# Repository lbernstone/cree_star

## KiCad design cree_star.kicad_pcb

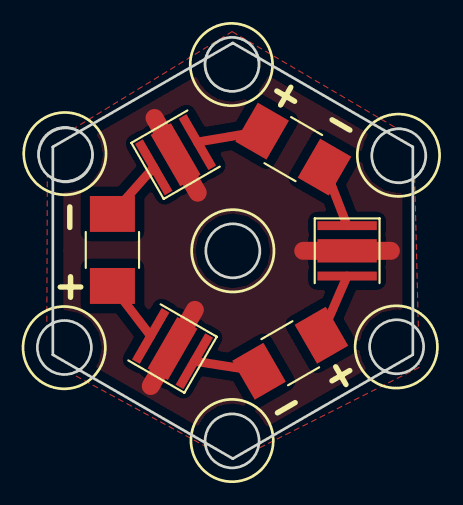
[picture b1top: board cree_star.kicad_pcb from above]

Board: 2 copper layers, 21.6 x 23.9 mm, 6 parts (0 on the bottom side), 6 nets.

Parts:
D1, D2, D3: LED; LED_Cree-XP-G
R1, R2, R3: R; R_1210_HandSoldering

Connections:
unnamed: D1.1, R1.2
unnamed: D1.2, R2.2
unnamed: D2.1, R3.1
unnamed: D2.2, R1.1
unnamed: D3.1, R2.1
unnamed: D3.2, R3.2
